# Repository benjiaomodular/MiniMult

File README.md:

# MiniMult
by Benjie Jiao

A simple passive 2HP mult. See docs in my website for more info: https://benjiaomodular.com/post/2022-02-15-mini-mult/.

## Versions
**1.0 - Initial version**
- All 7 jacks connected.

**1.1 - Minor tweaks**
- Split the jacks into 3 + 4 instead of having all of them connected together.

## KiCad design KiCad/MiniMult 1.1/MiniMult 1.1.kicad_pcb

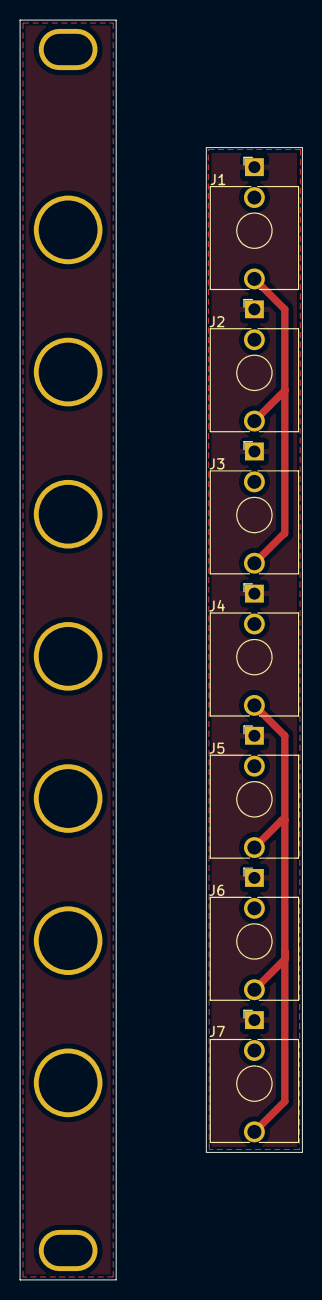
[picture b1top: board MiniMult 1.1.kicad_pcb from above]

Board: 2 copper layers, 28.8 x 128.5 mm, 7 parts (0 on the bottom side), 3 nets.

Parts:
J1, J2, J3, J4, J5, J6, J7: AudioJack2_SwitchT; AudioJack_3.5mm

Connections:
GND: J1.S, J2.S, J3.S, J4.S, J5.S, J6.S, J7.S
unnamed: J1.T, J2.T, J3.T
unnamed: J4.T, J5.T, J6.T, J7.T

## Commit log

2022-01-17 Added fabrication files
2022-01-17 Added readme
2022-01-17 Added some docs on versions
2022-01-17 Refined labels
2022-02-07 Added license file
2022-02-15 Added gerber files for v1.1
2022-02-15 Added link to website'
